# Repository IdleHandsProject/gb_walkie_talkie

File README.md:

# Ghost Bros Walkie-Talkie
## An open source "Fake" walkie-talkie for Fake Ghost Tours made by my friends in Vancouver.

When I say "Fake" walkie-talkie, what I mean is that this walkie-talkie does not do two way commincation. It actually doesn't even do one way communication(if you don't count the gps). 
This walkie-talkie was designed for my friends at Fake Ghost Tours [FakeGhostTours.com](http://fakeghosttours.com) - real friends not fake friends.

The purpose of the walkie-talkie is to be a GPS guided audio tour of fake ghost stories in Vancouver, British Columbia. 
Watch the video to see how it works, and why it was made. 
https://youtu.be/CiPm3to5vCE

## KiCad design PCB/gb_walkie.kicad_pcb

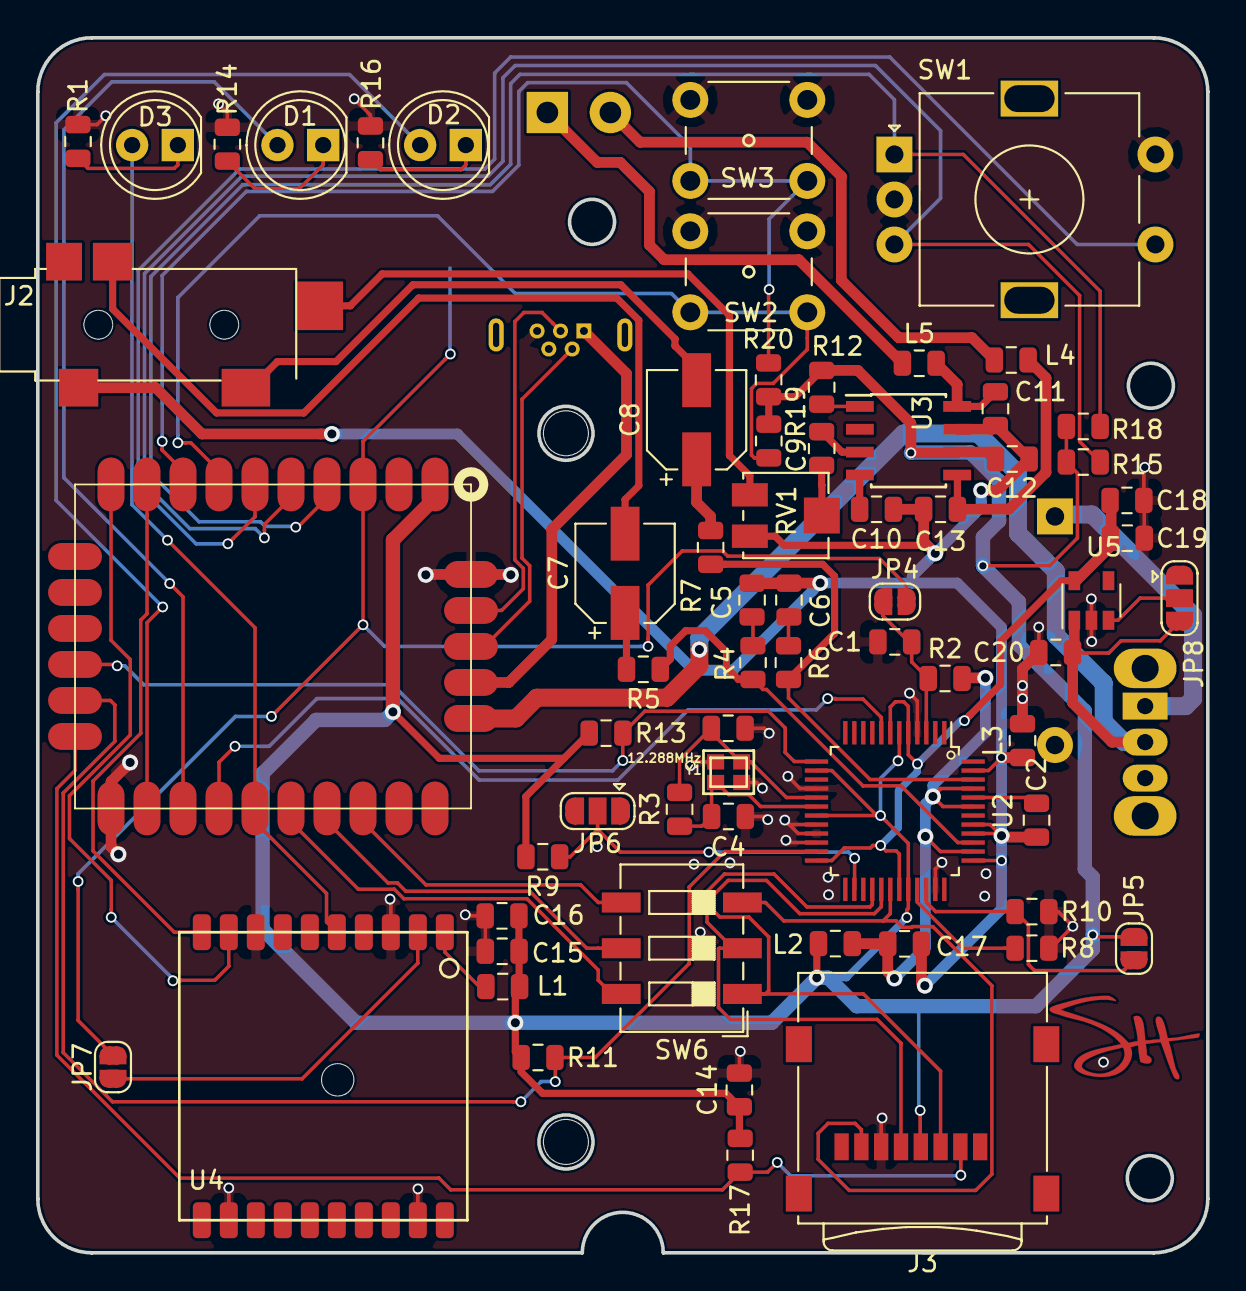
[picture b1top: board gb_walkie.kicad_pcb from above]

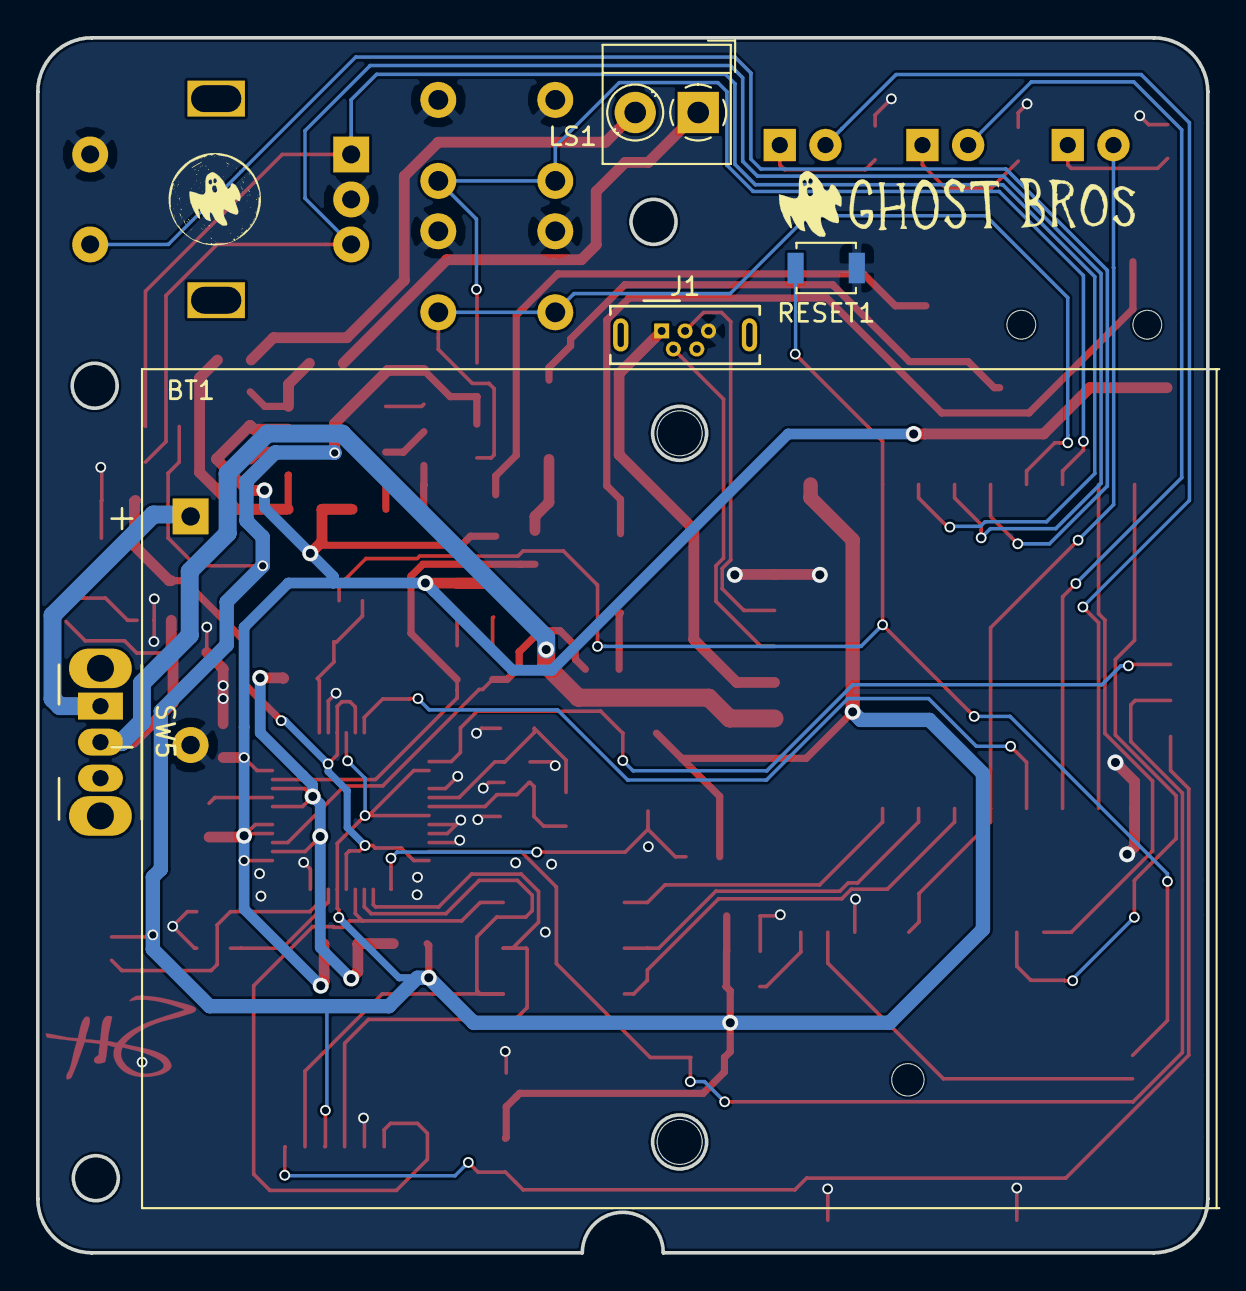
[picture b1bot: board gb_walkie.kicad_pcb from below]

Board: 2 copper layers, 65.0 x 67.5 mm, 71 parts (5 on the bottom side), 61 nets.

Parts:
BT1: Battery; BatteryHolder_BH3AAPC_3xAA
C1, C15, C17, C18: 0.1uF; C_0805_2012Metric
C2, C9, C10, C12, C14, C19, C20: 1uF; C_0805_2012Metric
C3, C4: 22pF; C_0805_2012Metric
C5, C6: 10nF; C_0805_2012Metric
C7, C8: 220uF; CP_Elec_5x5.3
C11, C13: 220pF; C_0805_2012Metric
C16: 10uF; C_0805_2012Metric
D1, D2, D3: LED; LED_D5.0mm
J1: USB_OTG; USB_Micro-B_Wuerth_614105150721_Vertical
J2: HPJACK; Jack_3.5mm_35RASMT4BHNTRX_Horizontal
J3: Micro_SD_Card; microSD_HC_Wuerth_693072010801
JP4, JP5, JP7: RST; SolderJumper-2_P1.3mm_Open_RoundedPad1.0x1.5mm
JP6: MP3RXSEL; SolderJumper-3_P1.3mm_Open_RoundedPad1.0x1.5mm
JP8: 1v8EN; SolderJumper-3_P1.3mm_Open_RoundedPad1.0x1.5mm
L1, L2: AFLTR; L_0805_2012Metric
L3: GFLTR; L_0805_2012Metric
L4, L5: SPFLTR; L_0805_2012Metric
LS1: Speaker; TerminalBlock_MetzConnect_Type059_RT06302HBWC_1x02_P3.50mm_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
R1, R14, R16: 1K; R_0805_2012Metric
R2, R8, R9, R10, R11, R13, R17: 100K; R_0805_2012Metric
R3: 1M; R_0805_2012Metric
R4, R5, R6, R7: 100R; R_0805_2012Metric
R12, R15, R18, R19, R20: 10K; R_0805_2012Metric
RESET1: RESET; SW_SPST_B3U-1000P
RV1: R_POT; Potentiometer_Bourns_3314J_Vertical
SW1: Rotary_Encoder_Switch; RotaryEncoder_Alps_EC11E-Switch_Vertical_H20mm
SW2, SW3: SW_Push; SW_PUSH_6mm_H13mm
SW5: POWER; SW_CuK_OS102011MA1QN1_SPDT_Angled
SW6: SW_DIP_x03; SW_DIP_SPSTx03_Slide_6.7x9.18mm_W6.73mm_P2.54mm_LowProfile_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
U1: SAMD21_MOD; SAMD_HCC_G_FOOT
U2: CODECODER-VS1053B(LQFP48); LQFP-48_7x7mm_P0.5mm
U3: PAM8302AAD; SOIC-8_3.9x4.9mm_P1.27mm
U4: FGPMM0PA6H; FGPMMOPA6H
U5: AP2127K-1.8; SOT-23-5
Y1: 12.288MHz; crystal_fa128

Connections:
3DFIX: D3.2, U1.21, U4.5
+1V8: C18.2, C19.2, U2.5, U2.7, U2.24, U2.31, U5.5
+3V3: C12.2, C14.2, C15.2, C16.2, J3.4, JP5.1, L1.2, L2.2, R9.2, R11.2, R12.2, R13.2, R15.2, R17.2, R18.2, R19.2, R20.2, U1.1, U2.6, U2.14, U2.19, U2.32, U3.6
+BATT: C20.2, JP8.3, SW5.2, U1.27, U5.1
AMPEN: R12.1, U3.1
DREQ: U1.20, U2.8
ENC1: R18.1, SW1.A, U1.4
ENC2: R15.1, SW1.B, U1.5
GND: BT1.2, C1.1, C3.1, C4.1, C14.1, C15.1, C16.1, C18.1, C19.1, C20.1, J1.5, J3.6, L3.2, R1.1, R8.1, R10.1, R14.1, R16.1, RESET1.1, SW1.C, SW1.S2, SW2.2, SW3.2, U1.17, U1.31, U2.4, U2.16, U2.20, U2.21, U2.22, U2.35, U4.3, U4.8, U4.12, U4.19, U5.2, Y1.2, Y1.4
GNDA: C2.2, C5.1, C6.1, C10.1, C11.2, C12.1, C13.2, C17.1, J2.S, L3.1, RV1.3, U2.37, U2.40, U2.41, U2.47, U3.7
GPIO0: R8.2, U2.33
GPIO1: JP5.2, R10.2, U2.34
LED2: D1.2, U1.19
LED3: D2.2, U1.18
LEFT: R6.2, R7.1, U2.46
L_AMP: J2.TN, RV1.1
L_OUT: C8.2, J2.T
MISO: J3.7, SW6.3, U2.30
MOSI: J3.3, SW6.1, U2.29
MP3CS: R11.1, U1.15, U2.23
MP3RST: C1.2, JP4.1, R2.1, U2.3
MP3RX: JP6.2, R9.1, U2.26
unnamed: BT1.1, SW5.1
unnamed: C2.1, U2.44
unnamed: C3.2, R3.2, U2.17, Y1.1
unnamed: C4.2, R3.1, U2.18, Y1.3
unnamed: C5.2, R4.1
unnamed: C6.2, R6.1
unnamed: C7.1, R5.2
unnamed: C8.1, R7.2
unnamed: C9.1, RV1.2
unnamed: C9.2, U3.3
unnamed: C10.2, U3.4
unnamed: C11.1, L5.2, U3.8
unnamed: C13.1, L4.2, U3.5
unnamed: D1.1, R14.2
unnamed: D2.1, R16.2
unnamed: D3.1, R1.2
unnamed: J1.1, U1.28
unnamed: J1.2, U1.29
unnamed: J1.3, U1.30
unnamed: JP7.2, U4.2
unnamed: JP8.2, U5.3
unnamed: L1.1, U4.1
unnamed: L4.1, LS1.2
unnamed: L5.1, LS1.1
unnamed: SW6.4, U1.24
unnamed: SW6.5, U1.23
unnamed: SW6.6, U1.22
PUSH1: SW1.S1, U1.6
PUSH2: R19.1, SW2.1, U1.7
PUSH3: R20.1, SW3.1, U1.8
RESET: JP4.2, JP7.1, RESET1.2, U1.3
RIGHT: R4.2, R5.1, U2.39
RXI: U1.10, U4.9
R_OUT: C7.2, J2.R
SCLK: J3.5, SW6.2, U2.28
SDCS: J3.2, R17.1, U1.16
TXO: U1.9, U4.10
VDDA: C17.2, L2.1, R2.2, U2.38, U2.43, U2.45
XDCS: R13.1, U1.14, U2.13

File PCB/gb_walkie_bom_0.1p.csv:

Component,Description,Part,References,Value,Footprint,Quantity Per PCB,Datasheet,Digikey Part No.,Digikey Part No. ,Field8,Field4,Field7,Field6,Field5
1,Battery (multiple cells),Battery,BT1,Battery,BatteryHolder_BH3AAPC_3xAA,1,~,BH3AA-PC-ND,,,,,,
2,Unpolarized capacitor,C_Small,C1 C15 C17 C18,0.1uF,C_0805_2012Metric,4,~,1276-1286-1-ND,,,,,,
3,Unpolarized capacitor,C_Small,C5 C6,10nF,C_0805_2012Metric,2,~,1276-1078-1-ND,,,,,,
4,Unpolarized capacitor,C_Small,C16,10uF,C_0805_2012Metric,1,~,311-1729-1-ND,,,,,,
5,Unpolarized capacitor,C_Small,C2 C9 C10 C12 C14 C19 C20,1uF,C_0805_2012Metric,7,~,587-1291-1-ND,,,,,,
6,Unpolarized capacitor,C_Small,C11 C13,220pF,C_0805_2012Metric,2,~,311-1123-1-ND,,,,,,
7,Polarised capacitor,CP1_Small,C7 C8,220uF,CP_Elec_5x5.3,2,~,P15078CT-ND,,,,,,
8,Unpolarized capacitor,C_Small,C3 C4,22pF,C_0805_2012Metric,2,~,478-3736-1-ND,,,,,,
9,LED generic,LED,D1 D2 D3,LED,LED_D5.0mm,3,~,,,,,,,
10,"D Audio Jack, 3 Poles (Stereo / TRS), Grounded Sleeve, Switched Poles (Normalling)",AudioJack3_Ground_Switch,J2,HPJACK,Jack_3.5mm_35RASMT4BHNTRX_Horizontal,1,~,SC1488-1-ND,,,,,,
11,Micro SD Card Socket,Micro_SD_Card,J3,Micro_SD_Card,microSD_HC_Wuerth_693072010801,1,http://katalog.we-online.de/em/datasheet/693072010801.pdf,732-3820-1-ND,,,,,,
12,USB mini/micro connector,USB_OTG,J1,USB_OTG,USB_Micro-B_Wuerth_614105150721_Vertical,1, ~,732-5958-1-ND,,,,,,
13,"Solder Jumper, 3-pole, open",SolderJumper_3_Open,JP8,1v8EN,SolderJumper-3_P1.3mm_Open_RoundedPad1.0x1.5mm,1,~,,,,,,,
14,"Solder Jumper, 3-pole, open",SolderJumper_3_Open,JP6,MP3RXSEL,SolderJumper-3_P1.3mm_Open_RoundedPad1.0x1.5mm,1,~,,,,,,,
15,"Jumper, normally open",Jumper_NO_Small,JP4 JP5 JP7,RST,SolderJumper-2_P1.3mm_Open_RoundedPad1.0x1.5mm,3,~,,,,,,,
16,Ferrite bead,Ferrite_Bead,L1 L2,AFLTR,L_0805_2012Metric,2,~,445-2164-1-ND,,,,,,
17,Ferrite bead,Ferrite_Bead,L3,GFLTR,L_0805_2012Metric,1,~,445-2164-1-ND,,,,,,
18,Ferrite bead,Ferrite_Bead,L4 L5,SPFLTR,L_0805_2012Metric,2,~,445-2164-1-ND,,,,,,
19,speaker,Speaker,LS1,Speaker,TerminalBlock_MetzConnect_Type059_RT06302HBWC_1x02_P3.50mm_Horizontal,1,~,,,,,,,
20,"Resistor, small symbol",R_Small,R2 R8 R9 R10 R11 R13 R17,100K,R_0805_2012Metric,7,~,,541-4164-1-ND,,,,,
21,"Resistor, small symbol",R_Small,R4 R5 R6 R7,100R,R_0805_2012Metric,4,~,,311-100ARCT-ND,,,,,
22,"Resistor, small symbol",R_Small,R12 R15 R18 R19 R20,10K,R_0805_2012Metric,5,~,,1276-5552-1-ND,,,,,
23,"Resistor, small symbol",R_Small,R1 R14 R16,1K,R_0805_2012Metric,3,~,311-1.0KARCT-ND,,,,,,
24,"Resistor, small symbol",R_Small,R3,1M,R_0805_2012Metric,1,~,,311-1.0MARCT-ND,,,,,
25,"Push button switch, generic, two pins",SW_Push,RESET1,RESET,SW_SPST_B3U-1000P,1,,SW1020CT-ND,,,,,,
26,Potentiometer,R_POT,RV1,R_POT,Potentiometer_Bourns_3314J_Vertical,1,~,445-2164-1-ND,,,,,,
27,"Switch, single pole double throw",SW_SPDT,SW5,POWER,SW_CuK_OS102011MA1QN1_SPDT_Angled,1,,CKN9565-ND,,,,,,
28,"Rotary encoder, dual channel, incremental quadrate outputs, with switch",Rotary_Encoder_Switch,SW1,Rotary_Encoder_Switch,RotaryEncoder_Alps_EC11E-Switch_Vertical_H20mm,1,~,PEC11R-4115F-S0018-ND,,,,,,
29,"3x DIP Switch, Single Pole Single Throw (SPST) switch, small symbol",SW_DIP_x03,SW6,SW_DIP_x03,SW_DIP_SPSTx03_Slide_6.7x9.18mm_W6.73mm_P2.54mm_LowProfile_JPin,1,,CT2193MST-ND,,,,,,
30,"Push button switch, generic, two pins",SW_Push,SW2 SW3,SW_Push,SW_PUSH_6mm_H13mm,2,,,,,,,,
31,"300mA low dropout linear regulator, shutdown pin, 2.5V-6V input voltage, 1.8V fixed positive output, SOT-23-5 package",AP2127K-1.8,U5,AP2127K-1.8,SOT-23-5,1,https://www.diodes.com/assets/Datasheets/AP2127.pdf,AP2112K-1.8TRG1DICT-ND,,,,,,
32,,CODECODER-VS1053B(LQFP48),U2,CODECODER-VS1053B(LQFP48),LQFP-48_7x7mm_P0.5mm,1,VS1053B MP3/WAV/OGG/MIDI Player & Recorder _CODEC_ Chip,,,VS1053B-L,Unavailable,None,VLSI,LQFP-48 VLSI
33,,FGPMM0PA6H,U4,FGPMM0PA6H,FGPMMOPA6H,1,,,,,,,,
34,"2.5W Filterless Class-D Mono Audio Amplifier, SOIC-8",PAM8302AAD,U3,PAM8302AAD,SOIC-8_3.9x4.9mm_P1.27mm,1,https://www.diodes.com/assets/Datasheets/PAM8302A.pdf,PAM8302AADCRDICT-ND,,,,,,
35,,SAMD21_MOD,U1,SAMD21_MOD,SAMD_HCC_G_FOOT,1,,,,,,,,
36,"Four pin crystal (GND on pins 2 and 4), e.g. in SMD package",Crystal_GND24,Y1,12.288MHz,crystal_fa128,1,~,535-10902-1-ND,,,,,,





Component Groups:,36
Component Count:,71
Fitted Components:,71
Number of PCBs:,1
Total components:,71
Schematic Version:,0.1p
Schematic Date:,2018-10-01
BoM Date:,10/10/2018 3:36:40 PM
Schematic Source:,\\HODGINSA-LAPTOP\Users\hodginsa\Documents\idlehandsdev\walkietalkie_ghostbros\PCB\gb_walkie.sch
KiCad Version:,Eeschema (5.0.0)

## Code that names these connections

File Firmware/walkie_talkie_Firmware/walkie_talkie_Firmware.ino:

/////////////////////////////////////////////////////////////
/*
   The FIRMWARE for the Ghost Bros Walkie Talkie Prop
   Watch the Build Video HERE -
   It uses GPS to determine your location and cue an audio file specific to that location.
   All audio files must be in the format of 8.3, (8 letters or numbers dot 3 letters or numbers - ex. AAAAA001.MP3)

   Created by Sean Hodgins 10/03/2018

   You can get the audio files from... INSERT WEBSITE
   The SD Card MUST contain the following files:
   intro000.mp3
   place001.mp3 through place013.mp3
   gpsstart.mp3
   gpsfound.mp3

  You can have unlimited (as SD Card permits) "random" sayings. You must declare the amount in the definition "randomTalkNum".
  Random talking can occur when the user is not close to a designated location.
  The random talk files will need to be named as:
  random00.mp3 - random99.mp3
  Do not skip any numbers.
*/


#include <TinyGPS++.h>
#include <SPI.h>
#include <SD.h>
#include <Adafruit_VS1053.h>

#define numLocations 11

#define randomTalkNum 2
int randomTalkPlayed[randomTalkNum] = {0};

//static const
double Loc_Lat[11] = {49.2843991, 49.283803, 49.283784, 49.283575, 49.283151, 49.283020, 49.283246, 49.283368, 49.283331, 49.283481, 49.283738};
//static const
double Loc_Lon[11] = { -123.1088747, -123.106501, -123.106359,  -123.106587, -123.105319, -123.104172, -123.104099, -123.103920, -123.104192, -123.104020, -123.105401};

char* trackLocation[] = {"place001.mp3", "place002.mp3", "place003.mp3", "place004.mp3", "place005.mp3", "place006.mp3", "place007.mp3", "place008.mp3", "place009.mp3", "place010.mp3", "place011.mp3"};

int distanceTo = 0;
int minimumDist = 50;

int CurrDest = 0;
int LastDest = 0;

#define LEDY 3
#define LEDR 4

#define Serial SerialUSB

#define BUTTTOP 9
#define BUTTBOT 10
#define BUTTENC 11

#define ENC1 13
#define ENC2 12
int encoderValue = 290;
int lastEncoded = 0;
int newA = 0;
int sum = 0;


#define XDCS A3
#define MP3CS A4
#define SDCS A5

#define PIN 1

int volume = 30;

// These are the pins used for the Audio
#define VS1053_RESET   -1     // VS1053 reset pin (not used!)
#define VS1053_CS       A4     // VS1053 chip select pin (output)
#define VS1053_DCS     A3     // VS1053 Data/command select pin (output)
#define CARDCS          A5     // Card chip select pin
// DREQ should be an Int pin *if possible* (not possible on 32u4)
#define VS1053_DREQ     5     // VS1053 Data request, ideally an Interrupt pin

Adafruit_VS1053_FilePlayer musicPlayer =
  Adafruit_VS1053_FilePlayer(VS1053_RESET, VS1053_CS, VS1053_DCS, VS1053_DREQ, CARDCS);


int inLocation = 0;
int currLocation = 0;
int notification = 0;
TinyGPSPlus gps;


int leastdistance = 0;

void setup()
{

  Loc_Lat[2] = 45.5540529;
  Loc_Lon[2] = -75.2820992;
  Serial.begin(115200);
  Serial1.begin(9600);
  //while (!Serial);
  pinMode(BUTTENC, INPUT_PULLUP);
  pinMode(BUTTTOP, INPUT);
  pinMode(BUTTBOT, INPUT);
  pinMode(LEDY, OUTPUT);
  pinMode(LEDR, OUTPUT);


  pinMode(ENC1, INPUT);
  pinMode(ENC2, INPUT);
  attachInterrupt(ENC1, updateEncoder, CHANGE);
  attachInterrupt(ENC2, updateEncoder, CHANGE);
  if (! musicPlayer.begin()) { // initialise the music player
    Serial.println(F("Couldn't find VS1053, do you have the right pins defined?"));
    while (1) {
      digitalWrite(LEDR, HIGH);
      delay(500);
      digitalWrite(LEDY, HIGH);
      delay(500);
      digitalWrite(LEDR, LOW);
      delay(500);
      digitalWrite(LEDY, LOW);
      delay(500);
    }
  }
  Serial.println(F("VS1053 found"));
  musicPlayer.setVolume(volume, 0);
  musicPlayer.sineTest(0x44, 200);    // Make a tone to indicate VS1053 is working
  digitalWrite(LEDY, HIGH);
  digitalWrite(LEDR, HIGH);
  delay(500);
  digitalWrite(LEDY, LOW);
  digitalWrite(LEDR, LOW);


  if (!SD.begin(CARDCS)) {
    Serial.println(F("SD failed, or not present"));
    while (1) {
      digitalWrite(LEDY, HIGH);
      delay(500);
      digitalWrite(LEDR, HIGH);
      delay(500);
      digitalWrite(LEDY, LOW);
      delay(500);
      digitalWrite(LEDR, LOW);
      delay(500);
    }
  }
  Serial.println("SD OK!");

  musicPlayer.setVolume(volume, 0);
  musicPlayer.useInterrupt(VS1053_FILEPLAYER_PIN_INT);  // DREQ int




  attachInterrupt(BUTTTOP, PLAY, FALLING);
  attachInterrupt(BUTTBOT, PAUSE, FALLING);
  attachInterrupt(BUTTENC, STOP, FALLING);

  delay(100);

  Serial.println(F("Searching for GPS"));
  musicPlayer.playFullFile("intro000.mp3");

  while (Serial1.available() > 0)
    gps.encode(Serial1.read());
  while (gps.location.isUpdated() == 0) {
    while (Serial1.available() > 0)
      gps.encode(Serial1.read());
    delay(100);
    Serial.println("Waiting for GPS");
    if (musicPlayer.stopped()) {
      //musicPlayer.startPlayingFile("waiting.mp3");
      //delay(100);
    }
  }

  musicPlayer.stopPlaying();
  Serial.println(F("GPS Found"));


}

void loop()
{
  if (musicPlayer.playingMusic == 1) {
    digitalWrite(LEDY, HIGH);
  }
  if (musicPlayer.stopped()) {
    digitalWrite(LEDY, LOW);
  }
  while (Serial1.available() > 0)
    gps.encode(Serial1.read());

  if (musicPlayer.stopped()) {
    if (gps.location.isValid())
    {
      int locationsum = 0;
      leastdistance = 5000000;
      for (int x = 0; x < numLocations; x++) {
        double distanceToLoc = TinyGPSPlus::distanceBetween(gps.location.lat(), gps.location.lng(), Loc_Lat[x], Loc_Lon[x]);
        int MetersTo = distanceToLoc;
        if (MetersTo < leastdistance){
          leastdistance = MetersTo;
        }
        if (MetersTo < 50) {

          locationsum++;
          currLocation = x;
          if (notification == 0) {
            notification = 1;
            Serial.print("In Location :");
            Serial.println(x);
            Serial.print("Distance: ");
            Serial.println(MetersTo);
          }
        }

      }
      if (locationsum > 0) {
        inLocation = 1;
        if (notification == 1) {
          digitalWrite(LEDR, HIGH);
          musicPlayer.sineTest(0x44, 200);
          notification = 2;
        }
      }
      else {
        inLocation = 0;
        digitalWrite(LEDR, LOW);
      }
    }
  }
  delay(100);
  while (musicPlayer.paused()) {
    for (int y = 255; y > 0; y--) {
      analogWrite(LEDY, y);
      delay(5);
    }
    for (int y = 0; y < 255; y++) {
      analogWrite(LEDY, y);
      delay(5);
    }
    pinMode(LEDY, OUTPUT);
  }

}



void DestChange() {

  int buttstate = digitalRead(4);
  while (buttstate == 0) {
    buttstate = digitalRead(4);
  }
  CurrDest = CurrDest + 1;
  if (CurrDest > 3) {
    CurrDest = 0;
  }
  if (LastDest != CurrDest) {

    LastDest = CurrDest;
  }
}

void PLAY() {
  int butt = digitalRead(BUTTTOP);
  while (butt == 0) {
    butt = digitalRead(BUTTTOP);
  }
  Serial.print("Distance: ");
  Serial.println(leastdistance);
  if (musicPlayer.stopped()) {
    if (inLocation == 1) {
      
      musicPlayer.startPlayingFile(trackLocation[currLocation]);
      notification = 0;
      digitalWrite(LEDY, 255);
    }
  }
}

void STOP() {
  int butt = digitalRead(BUTTENC);
  while (butt == 0) {
    butt = digitalRead(BUTTENC);
  }
  musicPlayer.stopPlaying();
  digitalWrite(LEDY, 0);
}

void PAUSE() {
  int butt = digitalRead(BUTTBOT);
  while (butt == 0) {
    butt = digitalRead(BUTTBOT);
  }
  if (! musicPlayer.paused()) {
    Serial.println("Paused");
    musicPlayer.pausePlaying(true);
  } else {
    Serial.println("Resumed");
    musicPlayer.pausePlaying(false);
  }

}

void VChange() {
  if (! musicPlayer.stopped()) {
    if (! musicPlayer.paused()) {
      musicPlayer.pausePlaying(true);
      Serial.print("Volume: ");
      Serial.println(volume);
      if (volume > 0 && volume < 60) {
        musicPlayer.setVolume(volume, 0);
      }
      musicPlayer.pausePlaying(false);
    }
  }
}


void updateEncoder() {
  int MSB = digitalRead(ENC1); //MSB = most significant bit
  int LSB = digitalRead(ENC2); //LSB = least significant bit

  int encoded = (MSB << 1) | LSB; //converting the 2 pin value to single number
  sum  = (lastEncoded << 2) | encoded; //adding it to the previous encoded value

  if (sum == 0b0010 || sum == 0b1101 || sum == 0b1011 || sum == 0b0100) {
    if (encoderValue > 0) {
      encoderValue--;
    }
  }
  if (sum == 0b1110 || sum == 0b1000 || sum == 0b0001 || sum == 0b0111) {
    if (encoderValue < 300) {
      encoderValue++;
    }
  }
  //Serial.println(encoderValue);
  volume = encoderValue / 5;

  VChange();
  lastEncoded = encoded; //store this value for next time
}

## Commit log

2018-10-21 Removed Sprue
2018-10-21 small changes
2018-10-21 updated component part number
2018-10-21 added black sticker
2018-10-21 added thingiverse STLs
